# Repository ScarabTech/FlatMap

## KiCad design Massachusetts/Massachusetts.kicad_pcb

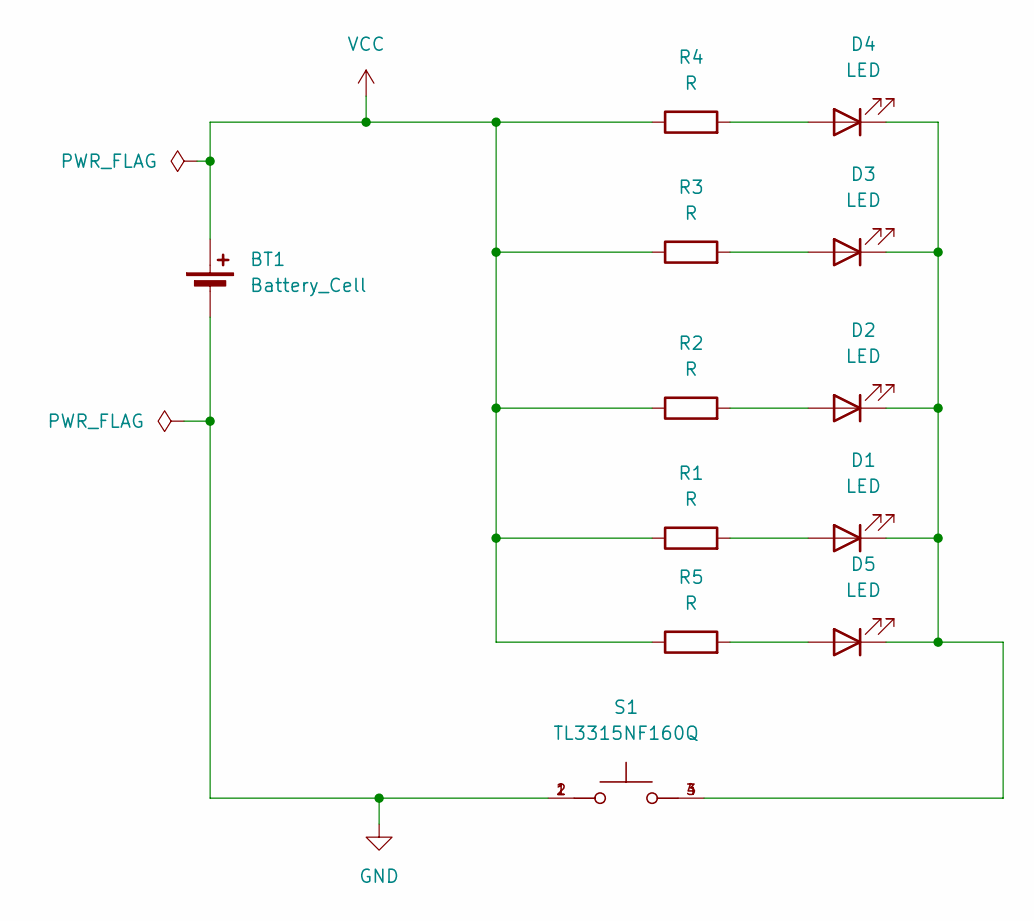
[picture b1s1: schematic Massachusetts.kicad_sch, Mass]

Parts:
BT1: Battery_Cell; BatteryHolder_Keystone_3034_1x20mm
D1, D2, D3, D4, D5: LED; LED_0603_1608Metric_Pad1.05x0.95mm_HandSolder
R1, R2, R3, R4, R5: R; R_0603_1608Metric_Pad0.98x0.95mm_HandSolder
S1: TL3315NF160Q; SW_TL3315NF160Q; PARTREV B

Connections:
GND: BT1.2 (-), S1.1, S1.2
unnamed: D1.2 (A), R1.2
unnamed: D1.1 (K), D2.1 (K), D3.1 (K), D4.1 (K), D5.1 (K), S1.3, S1.4
unnamed: D2.2 (A), R2.2
unnamed: D3.2 (A), R3.2
unnamed: D4.2 (A), R4.2
unnamed: D5.2 (A), R5.2
VCC: BT1.1 (+), R1.1, R2.1, R3.1, R4.1, R5.1

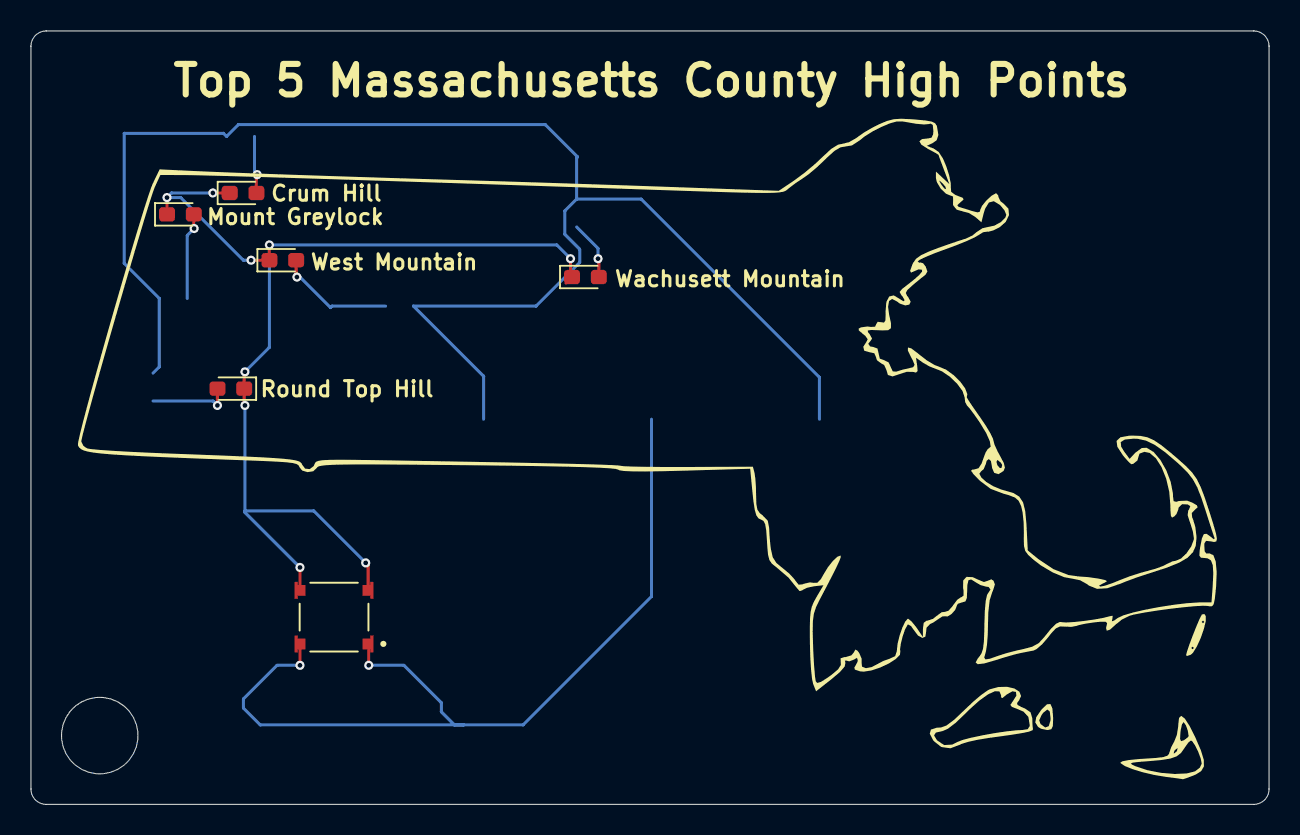
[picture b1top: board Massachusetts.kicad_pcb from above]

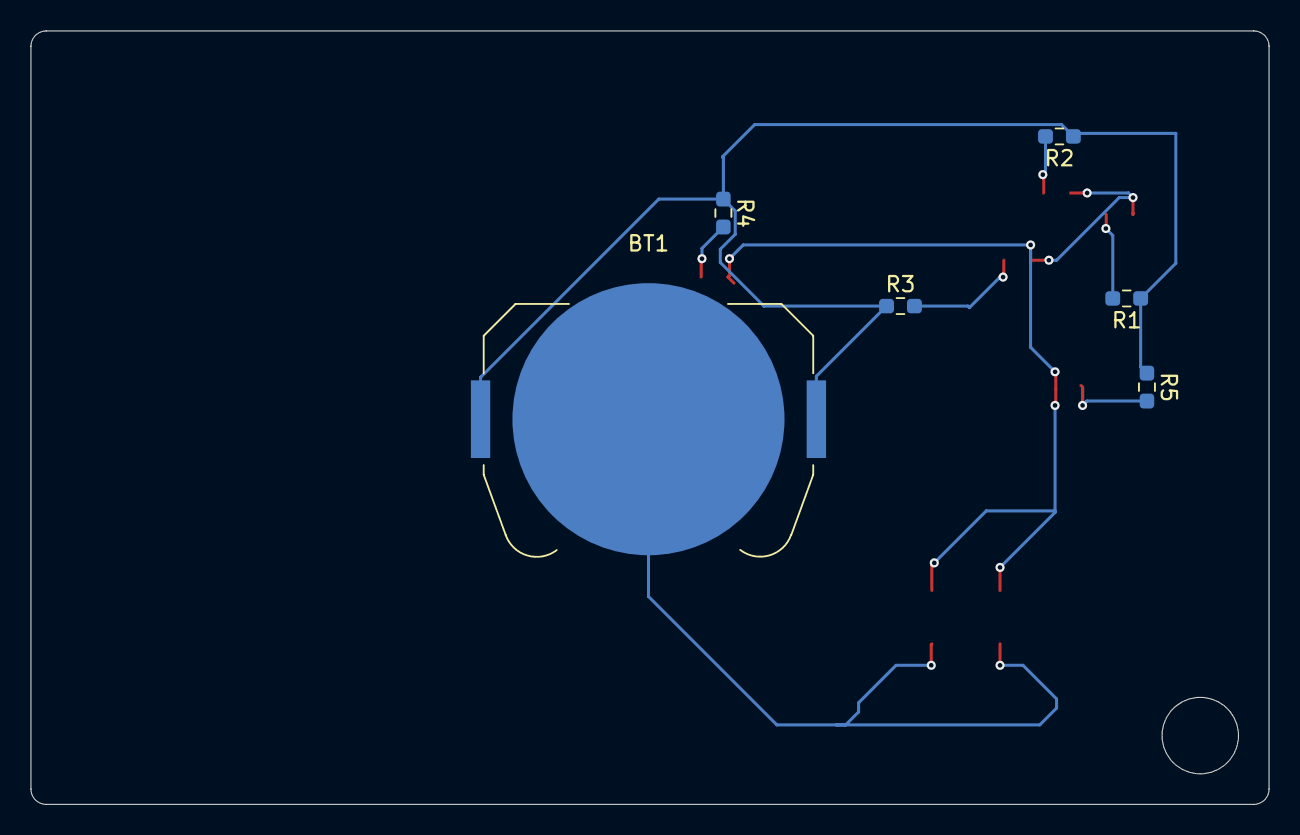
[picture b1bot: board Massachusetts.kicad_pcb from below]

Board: 2 copper layers, 81.0 x 50.6 mm, 12 parts (6 on the bottom side), 8 nets.

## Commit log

2025-07-01 Created Schematic and started PCB layout
2025-07-03 linked schematic symbols to footprints
2025-08-07 Added touch slider
2025-08-07 Added California
    Separate test MVP of same idea
2025-08-12 V1 ordered
2025-08-12 Added all US state DXFs
    Added all US state DXFs
2025-08-12 Added all US state DXFs (again)
    Added all US state DXFs (again)
2025-08-15 centered battery
